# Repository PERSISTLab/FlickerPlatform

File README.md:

Flicker Platform
======
 This repository hosts the Flicker platform acompanying the paper titled [*Flicker: Rapid Prototyping for the Batteryless Internet-of-Things*](http://josiahhester.com/cv/files/flickersensys.pdf) in the 15th ACM Conference on Embedded Networked Sensor Systems [(SenSys 2017)](http://sensys.acm.org/2017/).

This project is part of an ongoing collaboration between Clemson University and Northwestern University, originally initiated at Clemson under Prof. Jacob Sorber, with Josiah Hester.

## Setup and Usage

Please note that this is older hardware useful for posterity and documenting ideas. More modern platforms are currently in develop with richer documentation and examples.

## Contributors

- Diana Zhang and  Tamara Ortega contributed early on to the Flicker hardware designs for an REU in the summer of 2014.
- [Prof. Josiah Hester](http://josiahhester.com/cv/) guided the early effort and continued on after summer as a graduate student in the PERSIST Lab, implementing the compiler and supporting systems. Prof. Hester continues this work at Northwestern University.
- [Prof. Jacob Sorber](https://people.cs.clemson.edu/~jsorber/) oversaw, funded, and originated the project.

## Funding 

This research is based upon work supported by the National Science Foundation under grants [CNS-1453607](https://nsf.gov/awardsearch/showAward?AWD_ID=1453607) and [CCF-1539536](https://www.nsf.gov/awardsearch/showAward?AWD_ID=1539536) Any opinions, findings, and conclusions or recommendations expressed in this material are those of the authors and do not necessarily reflect the views of the National Science Foundation

## License

	MIT License
	Copyright 2017 Josiah Hester, Jacob Sorber, Clemson University

	Permission is hereby granted, free of charge, to any person obtaining a copy of this 
	software and associated documentation files (the "Software"), to deal in the Software 
	without restriction, including without limitation the rights to use, copy, modify, merge, 
	publish, distribute, sublicense, and/or sell copies of the Software, and to permit persons 
	to whom the Software is furnished to do so, subject to the following conditions:

	The above copyright notice and this permission notice shall be included in all copies or 
	substantial portions of the Software.

	THE SOFTWARE IS PROVIDED "AS IS", WITHOUT WARRANTY OF ANY KIND, EXPRESS OR IMPLIED, 
	INCLUDING BUT NOT LIMITED TO THE WARRANTIES OF MERCHANTABILITY, FITNESS FOR A PARTICULAR 
	PURPOSE AND NONINFRINGEMENT. IN NO EVENT SHALL THE AUTHORS OR COPYRIGHT HOLDERS BE LIABLE 
	FOR ANY CLAIM, DAMAGES OR OTHER LIABILITY, WHETHER IN AN ACTION OF CONTRACT, TORT OR 
	OTHERWISE, ARISING FROM, OUT OF OR IN CONNECTION WITH THE SOFTWARE OR THE USE OR OTHER 
	DEALINGS IN THE SOFTWARE.

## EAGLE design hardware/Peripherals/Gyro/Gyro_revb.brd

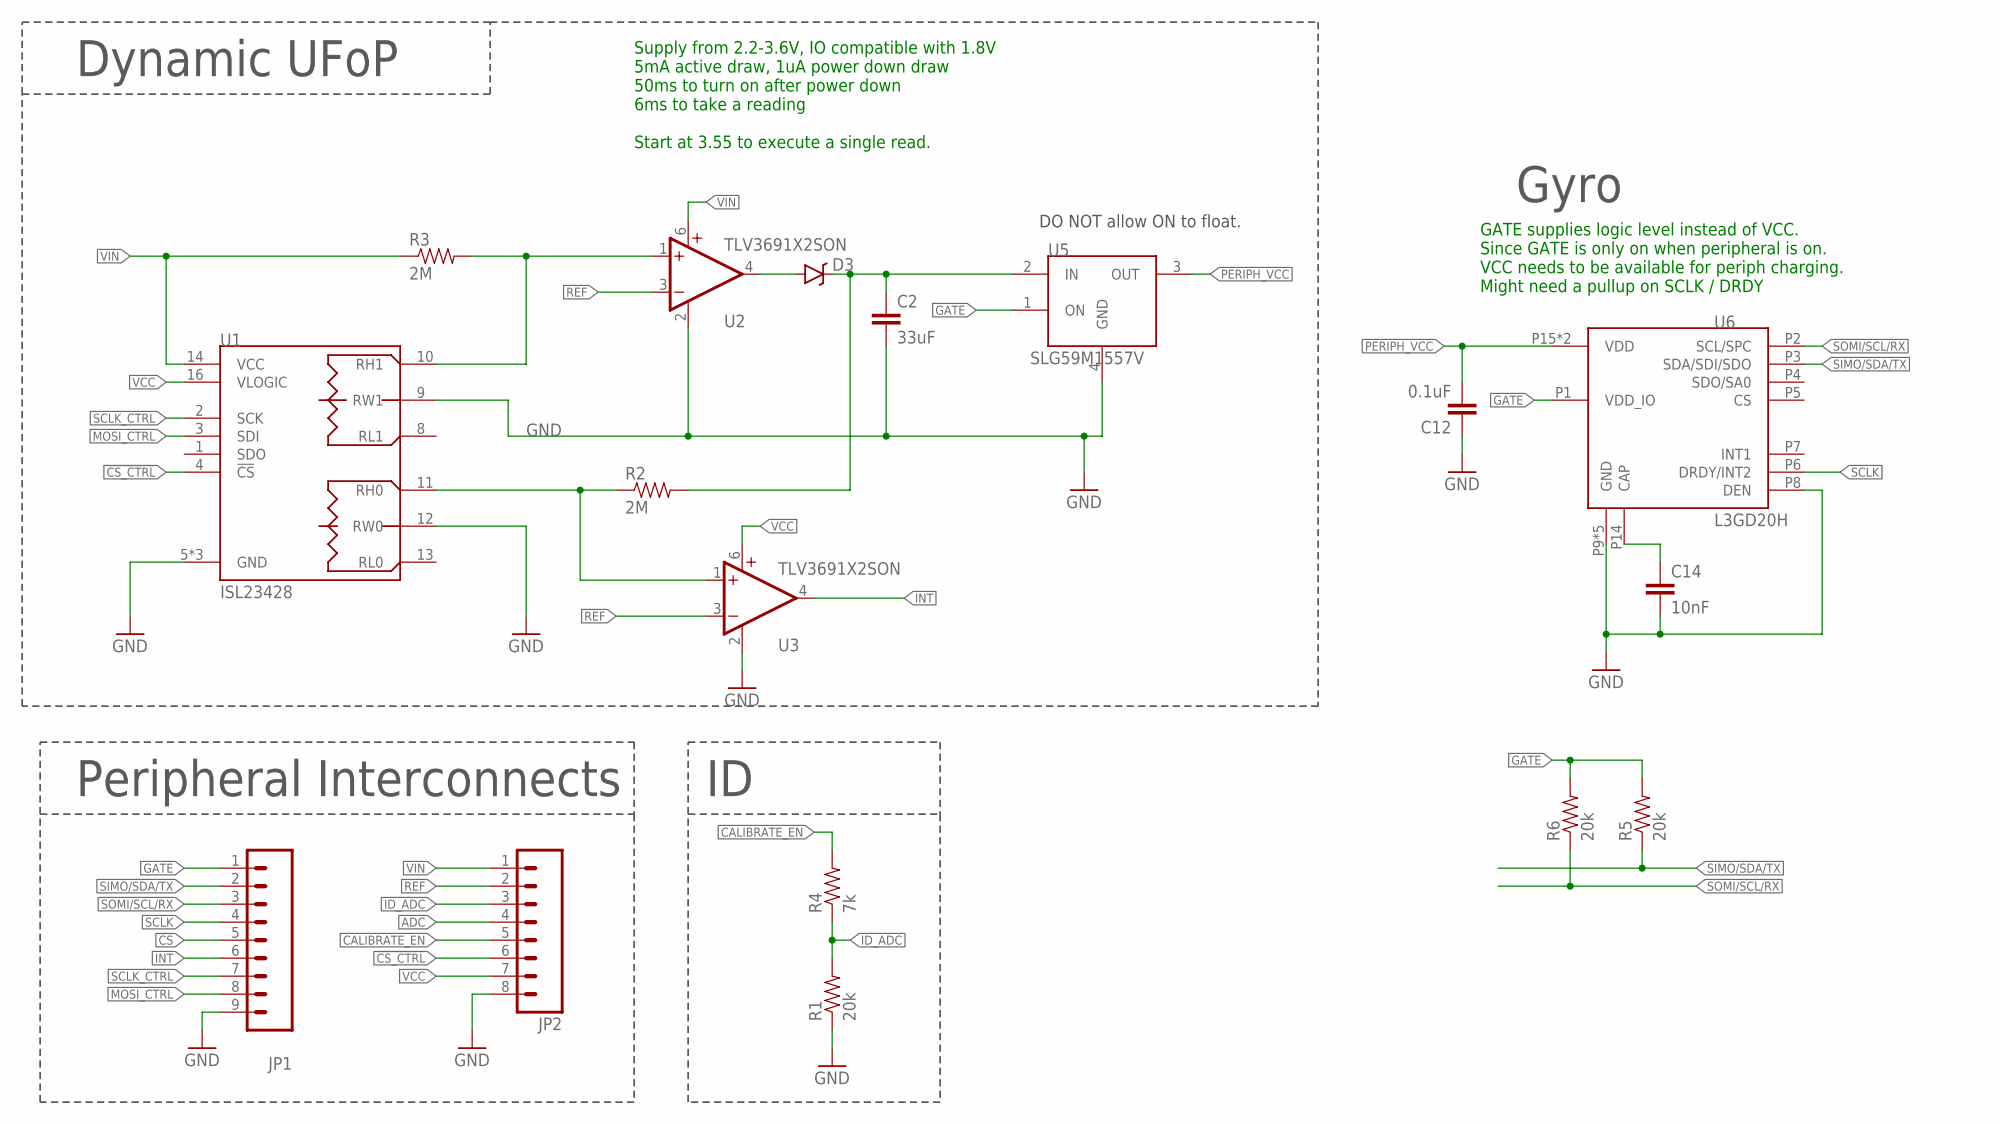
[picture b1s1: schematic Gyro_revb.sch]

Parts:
C2: 33uF; 1206; MPN C3216X5R0J336M130AC; DIGIKEY 445-4060-1-ND
C12: 0.1uF; 0402; MANAFACTURERPARTNUMBER 0402YD104KAT2A
C14: 10nF; 0402; MPN 0402YC103KAT2A
D3: RB751; SOD-523; MPN BAS40-02V-V-G-08; DIGIKEY BAS40-02V-V-G-08GICT-ND
JP1: M091.27MM; 1X09-1.27MM; MANUFACTURERPARTNUMBER GRPB091VWVN-RC; DIGIKEY S9014E-09-ND
JP2: M081.27MM; 1X08-1.27MM; MANUFACTURERPARTNUMBER GRPB081VWVN-RC; DIGIKEY S9014E-08-ND
R1, R5, R6: 20k; 0402; MPN ERJ-2RKF2002X
R2, R3: 2M; 0402; MPN RC1005F205CS; DIGIKEY 1276-4293-1-ND
R4: 7k; 0402; MPN RC0402FR-077K15L
U1: ISL23428; UTQFN-16; MPN ISL23428TFRUZ-T7A; DIGIKEY ISL23428TFRUZ-T7ACT-ND
U2, U3: TLV3691X2SON; X2SON; MPN TLV3691IDPFR; DIGIKEY 296-37242-1-ND
U5: SLG59M1557V; 4STDFN; MPN SLG59M1557V; MOUSER 402-SLG59M1557V
U6: L3GD20H; LGA16L; MPN L3GD20HTR; DIGIKEY 497-13931-1-ND

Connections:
!CS: JP1.5
!CS_CTRL: JP2.6, U1.4 (!CS)
ADC: JP2.4
CALIBRATE_EN: JP2.5, R4.2
GATE: JP1.1, R5.2, R6.2, U5.1 (ON), U6.P1 (VDD_IO)
GND: C2.2, C12.1, C14.2, JP1.9, JP2.8, R1.1, U1.5 (GND), U1.6 (GND), U1.9 (RW1), U1.12 (RW0), U1.15 (GND), U2.2 (GND), U3.2 (GND), U5.4 (GND), U6.P8 (DEN), U6.P9 (GND), U6.P10 (GND), U6.P11 (GND), U6.P12 (GND), U6.P13 (GND)
ID_ADC: JP2.3, R1.2, R4.1
INT: JP1.6, U3.4 (OUT)
MOSI_CTRL: JP1.8, U1.3 (SDI)
unnamed: D3.A, U2.4 (OUT)
unnamed: C2.1, D3.C, R2.2, U5.2 (IN)
unnamed: R3.2, U1.10 (RH1), U2.1 (+IN)
unnamed: R2.1, U1.11 (RH0), U3.1 (+IN)
unnamed: C14.1, U6.P14 (CAP)
PERIPH_VCC: C12.2, U5.3 (OUT), U6.P15 (VDD), U6.P16 (VDD)
REF: JP2.2, U2.3 (-IN), U3.3 (-IN)
SCLK: JP1.4, U6.P6 (DRDY/INT2)
SCLK_CTRL: JP1.7, U1.2 (SCK)
SIMO/SDA/TX: JP1.2, R5.1, U6.P3 (SDA/SDI/SDO)
SOMI/SCL/RX: JP1.3, R6.1, U6.P2 (SCL/SPC)
VCC: JP2.7, U1.16 (VLOGIC), U3.6 (V+)
VIN: JP2.1, R3.1, U1.14 (VCC), U2.6 (V+)

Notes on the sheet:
DO NOT allow ON to float.
Peripheral Interconnects
Dynamic UFoP
Gyro
GATE supplies logic level instead of VCC. Since GATE is only on when peripheral is on. VCC needs to be available for periph charging. Might need a pullup on SCLK / DRDY
Supply from 2.2-3.6V, IO compatible with 1.8V 5mA active draw, 1uA power down draw 50ms to turn on after power down 6ms to take a reading Start at 3.55 to execute a single read.

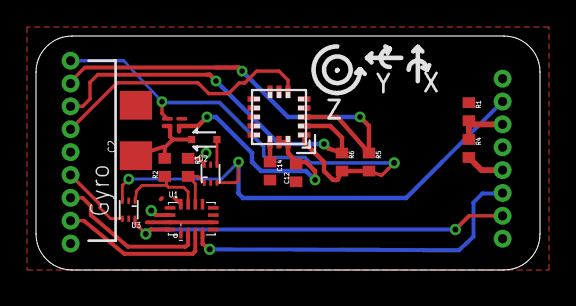
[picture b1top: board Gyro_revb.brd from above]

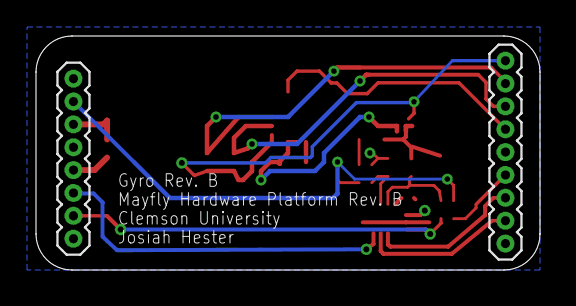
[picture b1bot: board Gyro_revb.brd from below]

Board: 2 copper layers, 28.0 x 13.0 mm, 17 parts (2 on the bottom side), 20 nets.

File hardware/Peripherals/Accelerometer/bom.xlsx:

Part | Value | Device | Package | Description | DIGIKEY | MPN
C2 | 2.2uF | C-EU0603 | 603 |  | 587-1430-1-ND | EMK107BJ225KA-T
C12 | 0.1uF | C-EU | 402 |  |  | 0402YD104KAT2A
D3 | RB751 | DIODE-SCHOTTKY-RB751 | SOD-523 | Schottky diodes in SFE's production catalog | BAS40-02V-V-G-08GICT-ND | BAS40-02V-V-G-08
JP1 |  | M091.27MM | 1X09-1.27MM | Header 9 | S9014E-09-ND | GRPB091VWVN-RC
JP2 |  | M081.27MM | 1X08-1.27MM | Header 8 | S9014E-08-ND | GRPB081VWVN-RC
R1 | 20k | R-EU | 402 |  |  | ERJ-2RKF2002X
R2 | 2M | R-EU | 402 |  | 1276-4293-1-ND | RC1005F205CS
R3 | 2M | R-EU | 402 |  | 1276-4293-1-ND | RC1005F205CS
R4 | 1k | R-EU | 402 |  |  | ERJ-2RKF1001X
U1 | ISL23428 | ISL23428 | UTQFN-16 | Intersil: Dual, 128-Tap, Low Voltage Digitally Controlled | ISL23428TFRUZ-T7ACT-ND | ISL23428TFRUZ-T7A
U2 | TLV3691X2SON | TLV3691X2SON | X2SON | 0.9-V to 6.5-V, Nanopower Comparator | 296-37242-1-ND | TLV3691IDPFR
U3 | TLV3691X2SON | TLV3691X2SON | X2SON | 0.9-V to 6.5-V, Nanopower Comparator | 296-37242-1-ND | TLV3691IDPFR
U4 | ADXL362 | ADXL362 | ADXL362 | Micropower 3-axis accelerometer | ADXL362BCCZ-RL7CT-ND | ADXL362BCCZ-RL7
;";";
U5 | SLG59M1557V | SLG59M1557V | 4STDFN | SILEGO SLG59M1557V: Ultra-small 28.5 mŒ©, 1.0 A |  | SLG59M1557V

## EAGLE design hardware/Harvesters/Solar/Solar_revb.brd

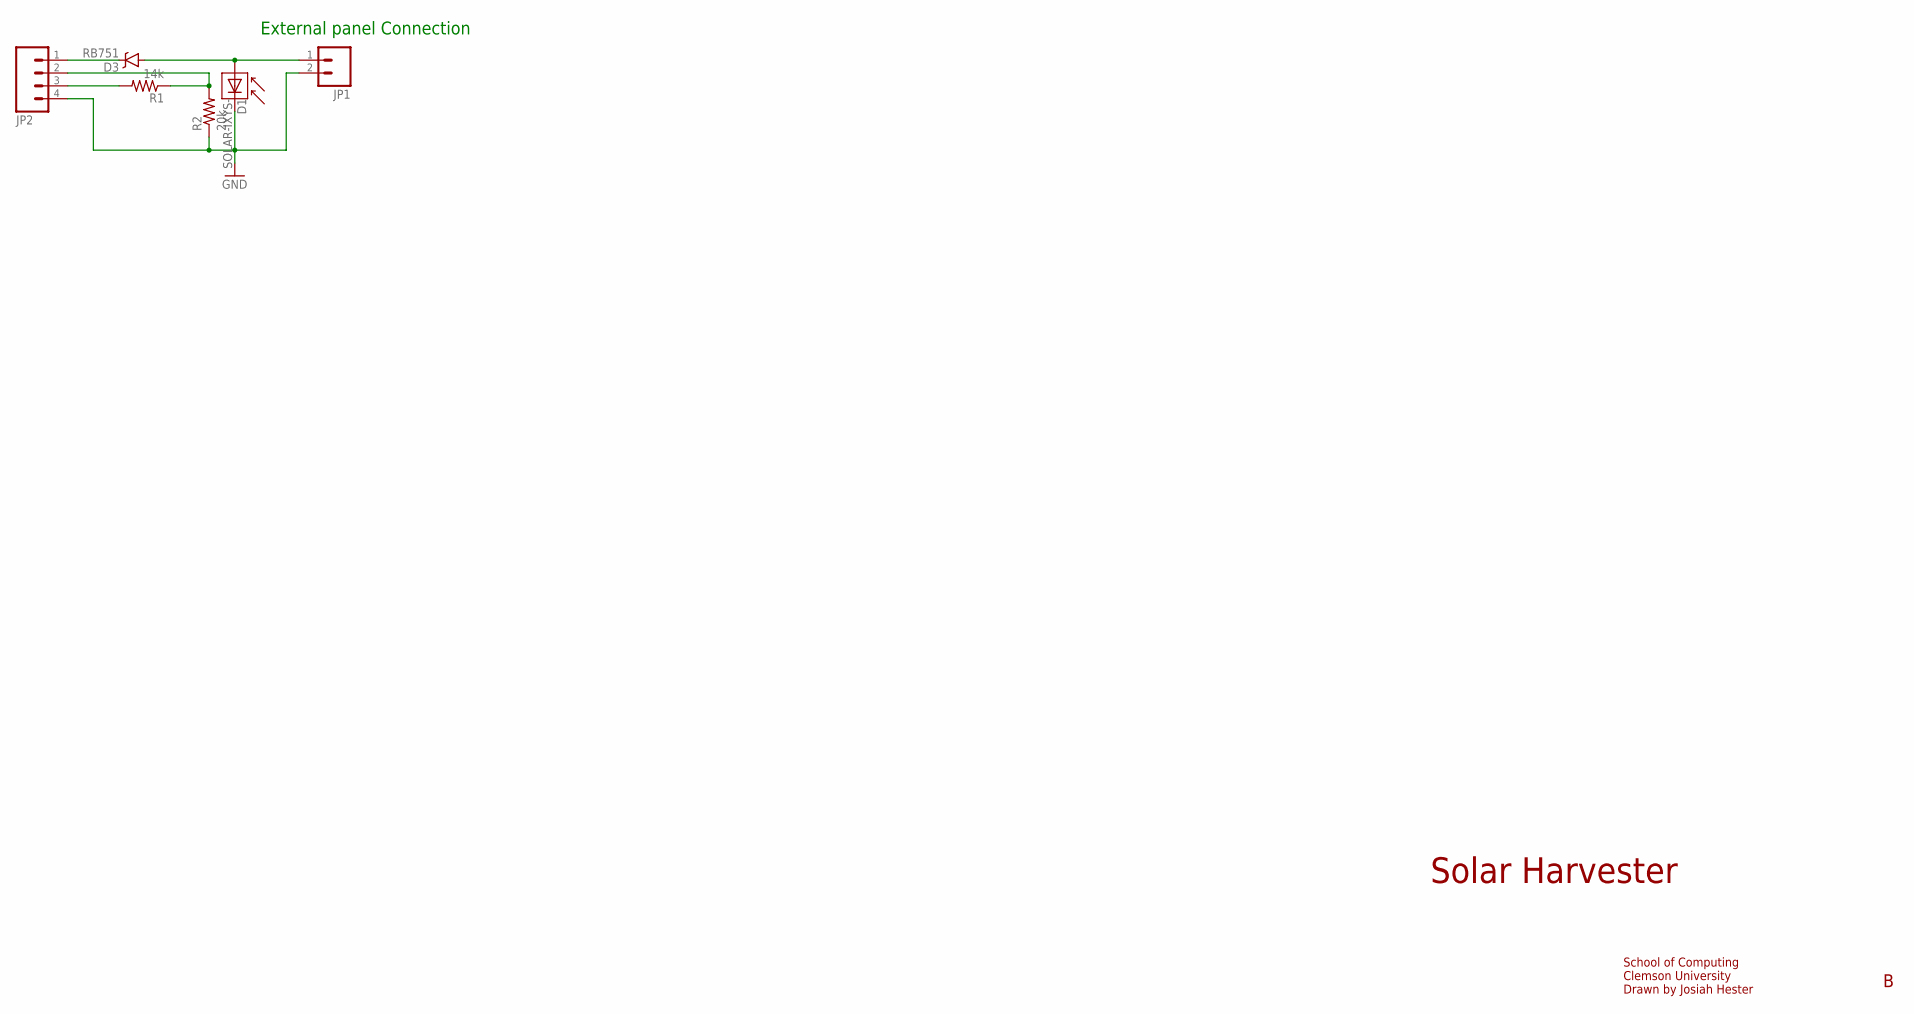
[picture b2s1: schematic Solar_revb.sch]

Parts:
D1: SOLAR-IXYS-; SOLARBIT-12X1; DIGIKEY KXOB22-01X8F-ND
D3: RB751; SOD-523; MPN BAS40-02V-V-G-08
JP1: M02LOCK; 1X02_LOCK
JP2: M041.27MM; 1X04-1.27MM; MPN GRPB041VWVN-RC
R1: 14k; 0603; MPN CRCW060314K0FKEA
R2: 20k; 0603; MPN CRCW060320K0FKEA

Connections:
GND: D1.- (C), JP1.2, JP2.4, R2.1
unnamed: JP2.2, R1.1, R2.2
unnamed: D1.+ (A), D3.A, JP1.1
unnamed: JP2.3, R1.2
unnamed: D3.C, JP2.1

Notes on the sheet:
Solar Harvester
School of Computing Clemson University Drawn by Josiah Hester
External panel Connection

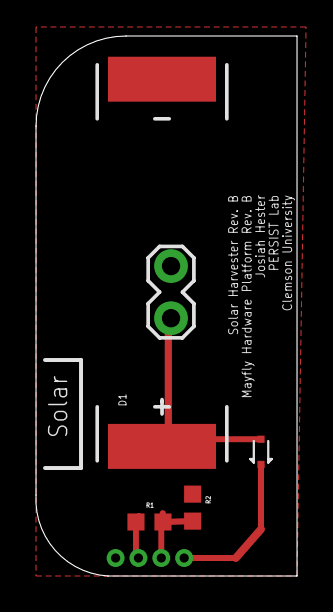
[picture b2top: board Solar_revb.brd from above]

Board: 2 copper layers, 14.5 x 30.0 mm, 6 parts (1 on the bottom side), 5 nets.

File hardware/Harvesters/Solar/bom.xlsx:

Part | Value | Device | Package | Description | DIGIKEY | MPN | PROD_ID | VALUE
D1 | SOLAR-IXYS- | SOLAR-IXYS- | SOLARBIT-12X1 |  | KXOB22-01X8F-ND
D3 | RB751 | DIODE-SCHOTTKY-RB751 | SOD-523 | Schottky diodes in SFE's production catalog |  | BAS40-02V-V-G-08 | DIO-11018 | RB751
JP1 |  | M02LOCK | 1X02_LOCK | Standard 2-pin 0.1 header. Use with"
JP2 |  | M041.27MM | 1X04-1.27MM | Header 4 |  | GRPB041VWVN-RC
R1 | 14k | R-EU0603 | 603 |  |  | CRCW060314K0FKEA
R2 | 20k | R-EU0603 | 603 |  |  | CRCW060320K0FKEA

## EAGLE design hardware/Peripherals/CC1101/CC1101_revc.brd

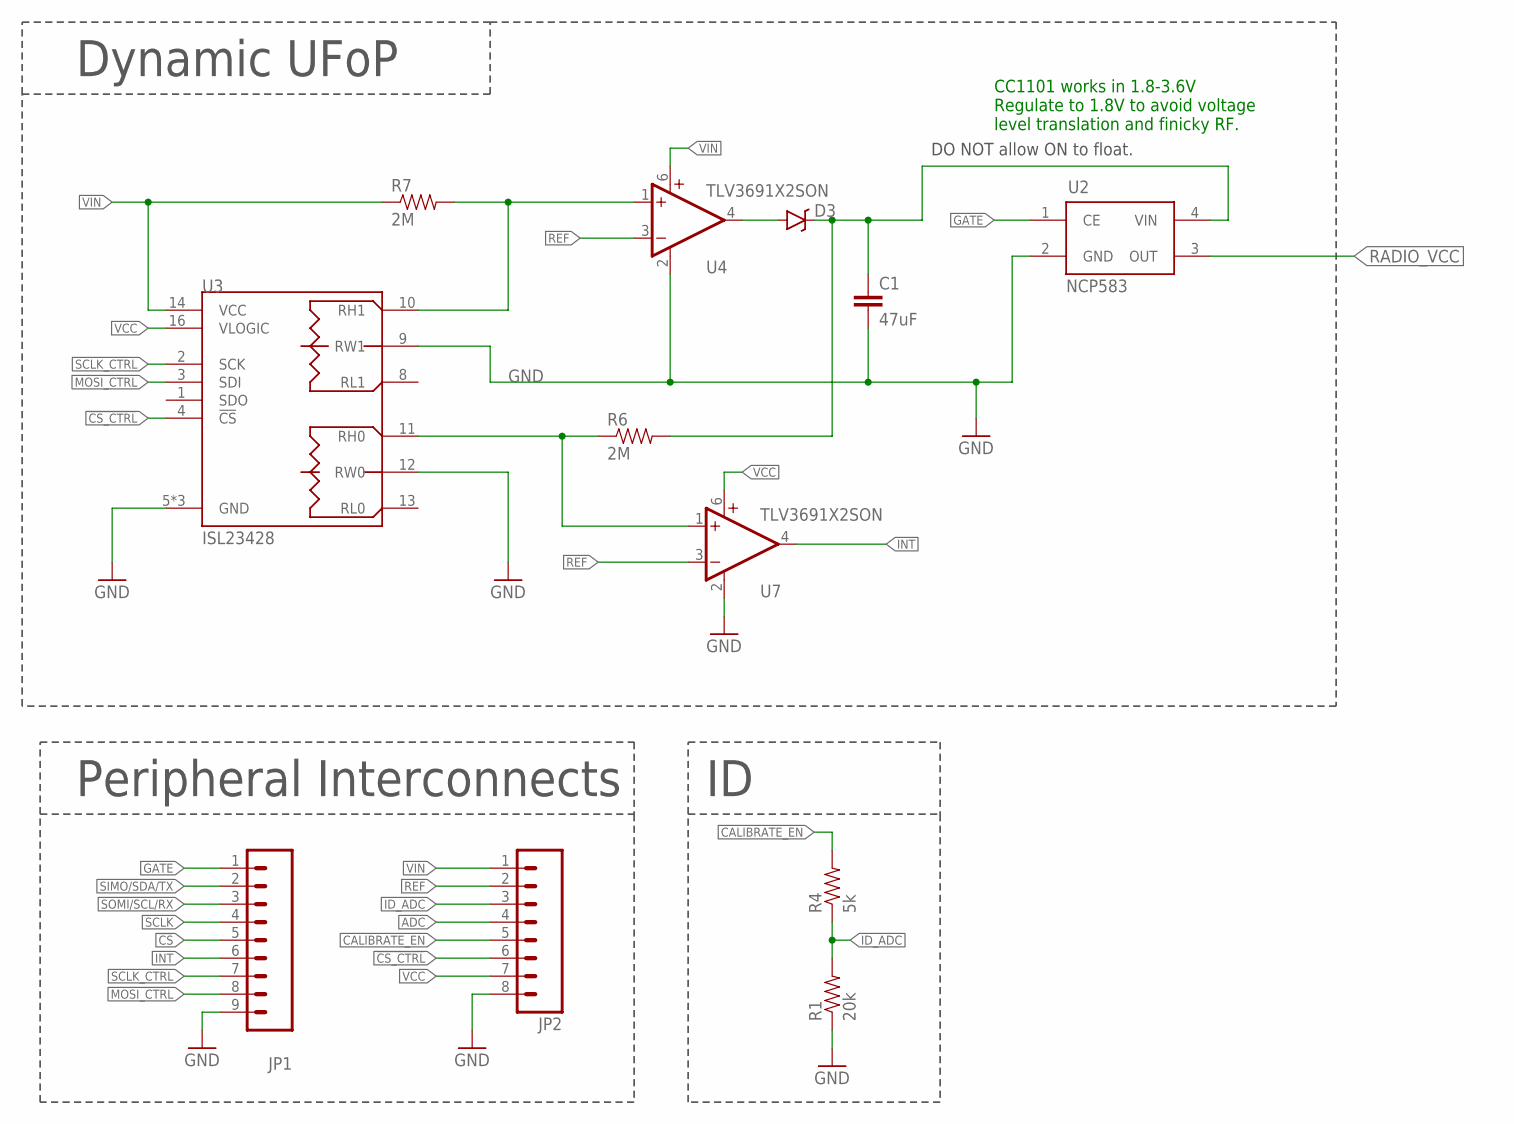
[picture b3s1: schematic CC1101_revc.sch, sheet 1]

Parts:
C1: 47uF; 1206; MPN GRM31CR60J476ME19L; DIGIKEY 490-3907-1-ND
D3: RB751; SOD-523; MPN RB751S40T1G; DIGIKEY BAS40-02V-V-G-08GICT-ND
JP1: M091.27MM; 1X09-1.27MM; MPN GRPB091VWVN-RC
JP2: M081.27MM; 1X08-1.27MM; MPN GRPB081VWVN-RC
R1: 20k; 0402; MPN ERJ-2RKF2002X
R4: 5k; 0402; MPN ERJ-2RKF4991X
R6, R7: 2M; 0402; MPN RC1005F205CS; DIGIKEY 1276-4293-1-ND
U2: NCP583; SC82-AB_1PRIMARY; MPN NCP583SQ18T1G; DIGIKEY NCP583SQ18T1GOSCT-ND
U3: ISL23428; UTQFN-16; MPN ISL23428TFRUZ-T7A; DIGIKEY ISL23428TFRUZ-T7ACT-ND
U4, U7: TLV3691X2SON; X2SON; MPN TLV3691IDPFR; DIGIKEY 296-37242-1-ND

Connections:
!CS: JP1.5; also elsewhere on the board
!CS_CTRL: JP2.6, U3.4 (!CS)
ADC: JP2.4
CALIBRATE_EN: JP2.5, R4.2
GATE: JP1.1, U2.1 (CE)
GND: C1.2, JP1.9, JP2.8, R1.1, U2.2 (GND), U3.5 (GND), U3.6 (GND), U3.9 (RW1), U3.12 (RW0), U3.15 (GND), U4.2 (GND), U7.2 (GND); also elsewhere on the board
ID_ADC: JP2.3, R1.2, R4.1
INT: JP1.6, U7.4 (OUT)
MOSI_CTRL: JP1.8, U3.3 (SDI)
unnamed: R7.2, U3.10 (RH1), U4.1 (+IN)
unnamed: R6.1, U3.11 (RH0), U7.1 (+IN)
unnamed: D3.A, U4.4 (OUT)
PERIPH_VCC: C1.1, D3.C, R6.2, U2.4 (VIN)
RADIO_VCC: U2.3 (OUT); also elsewhere on the board
REF: JP2.2, U4.3 (-IN), U7.3 (-IN)
SCLK: JP1.4; also elsewhere on the board
SCLK_CTRL: JP1.7, U3.2 (SCK)
SIMO/SDA/TX: JP1.2; also elsewhere on the board
SOMI/SCL/RX: JP1.3; also elsewhere on the board
VCC: JP2.7, U3.16 (VLOGIC), U7.6 (V+)
VIN: JP2.1, R7.1, U3.14 (VCC), U4.6 (V+)

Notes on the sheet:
Peripheral Interconnects
Dynamic UFoP
DO NOT allow ON to float.
CC1101 works in 1.8-3.6V Regulate to 1.8V to avoid voltage level translation and finicky RF.

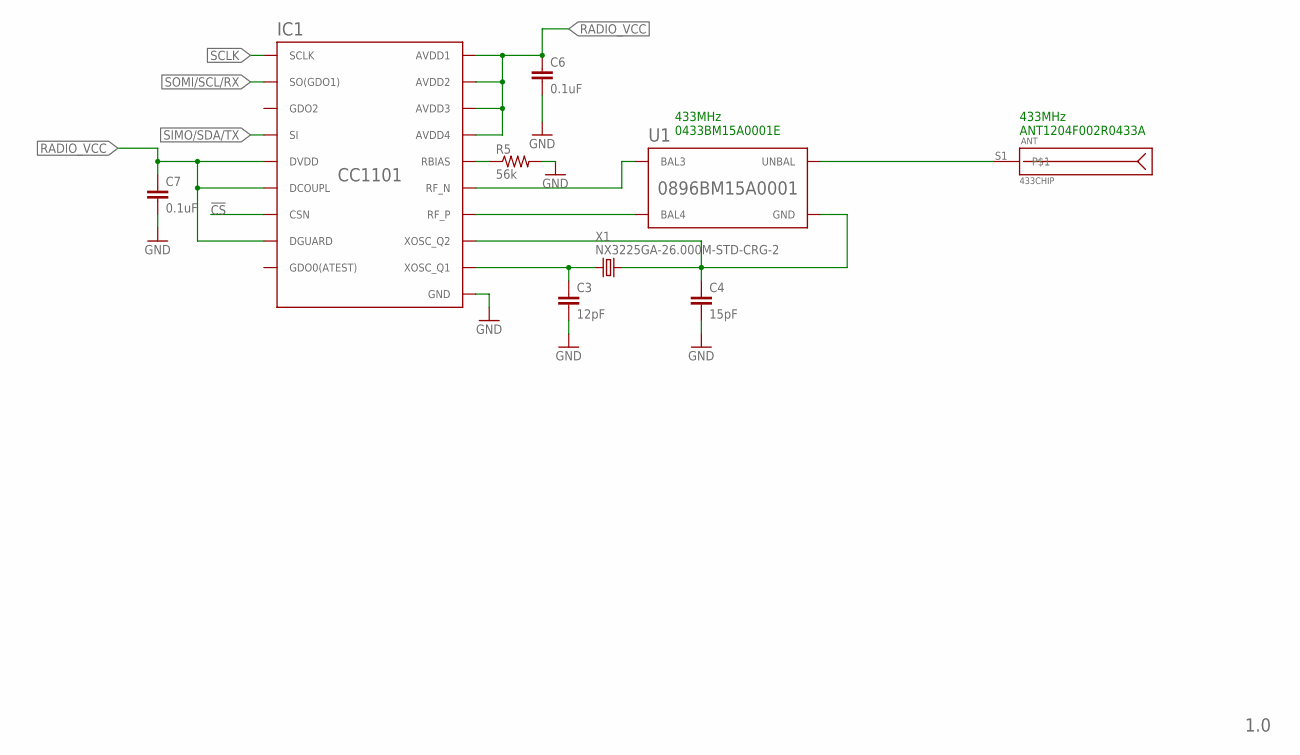
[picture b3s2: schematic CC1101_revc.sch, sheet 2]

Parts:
ANT: 433CHIP; ANT-433-USP; MPN ANT1204F002R0433A
C3: 12pF; 0603; MPN 06035A120FAT2A
C4: 15pF; 0603; MPN C1608C0G1H150J080AA
C6, C7: 0.1uF; 0603; MPN GCJ188R71H104KA12D
IC1: CC1101; QLP20; MPN CC1101RGP
R5: 56k; 0603; MPN ERJ-3GEYJ563V
U1: 0896BM15A0001; MPN 0433BM15A0001E
X1: NX3225GA-26.000M-STD-CRG-2; XTAL-3.2X2.5; MPN NX3225GA-26.000M-STD-CRG-2

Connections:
!CS: IC1.7 (CSN); also elsewhere on the board
GND: C3.2, C4.2, C6.2, C7.2, IC1.16 (GND), IC1.19 (GND), IC1.GND, R5.2; also elsewhere on the board
unnamed: IC1.12 (RF_P), U1.4 (BAL4)
unnamed: IC1.13 (RF_N), U1.3 (BAL3)
unnamed: C3.1, IC1.8 (XOSC_Q1), X1.1
unnamed: IC1.17 (RBIAS), R5.1
unnamed: ANT.S1, U1.1 (UNBAL)
RADIO_VCC: C6.1, C7.1, IC1.4 (DVDD), IC1.5 (DCOUPL), IC1.9 (AVDD1), IC1.11 (AVDD2), IC1.14 (AVDD3), IC1.15 (AVDD4), IC1.18 (DGUARD); also elsewhere on the board
SCLK: IC1.1 (SCLK); also elsewhere on the board
SIMO/SDA/TX: IC1.20 (SI); also elsewhere on the board
SOMI/SCL/RX: IC1.2 (SO(GDO1)); also elsewhere on the board
XOSC_Q2: C4.1, IC1.10 (XOSC_Q2), U1.2 (GND), U1.5 (GND), U1.6 (GND), X1.3 (2)

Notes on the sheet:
433MHz 0433BM15A0001E
1.0
433MHz ANT1204F002R0433A

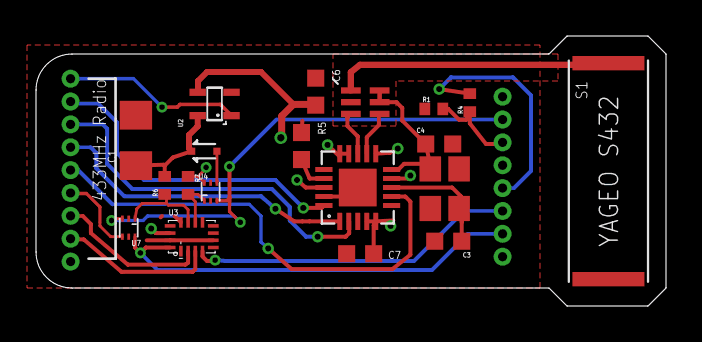
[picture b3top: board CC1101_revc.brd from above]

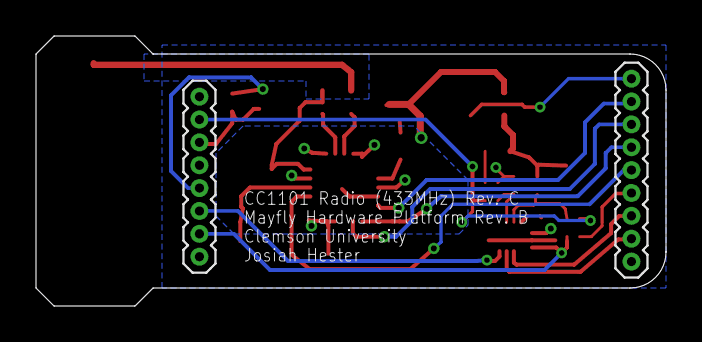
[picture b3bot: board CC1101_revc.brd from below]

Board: 2 copper layers, 35.0 x 15.0 mm, 21 parts (2 on the bottom side), 26 nets.

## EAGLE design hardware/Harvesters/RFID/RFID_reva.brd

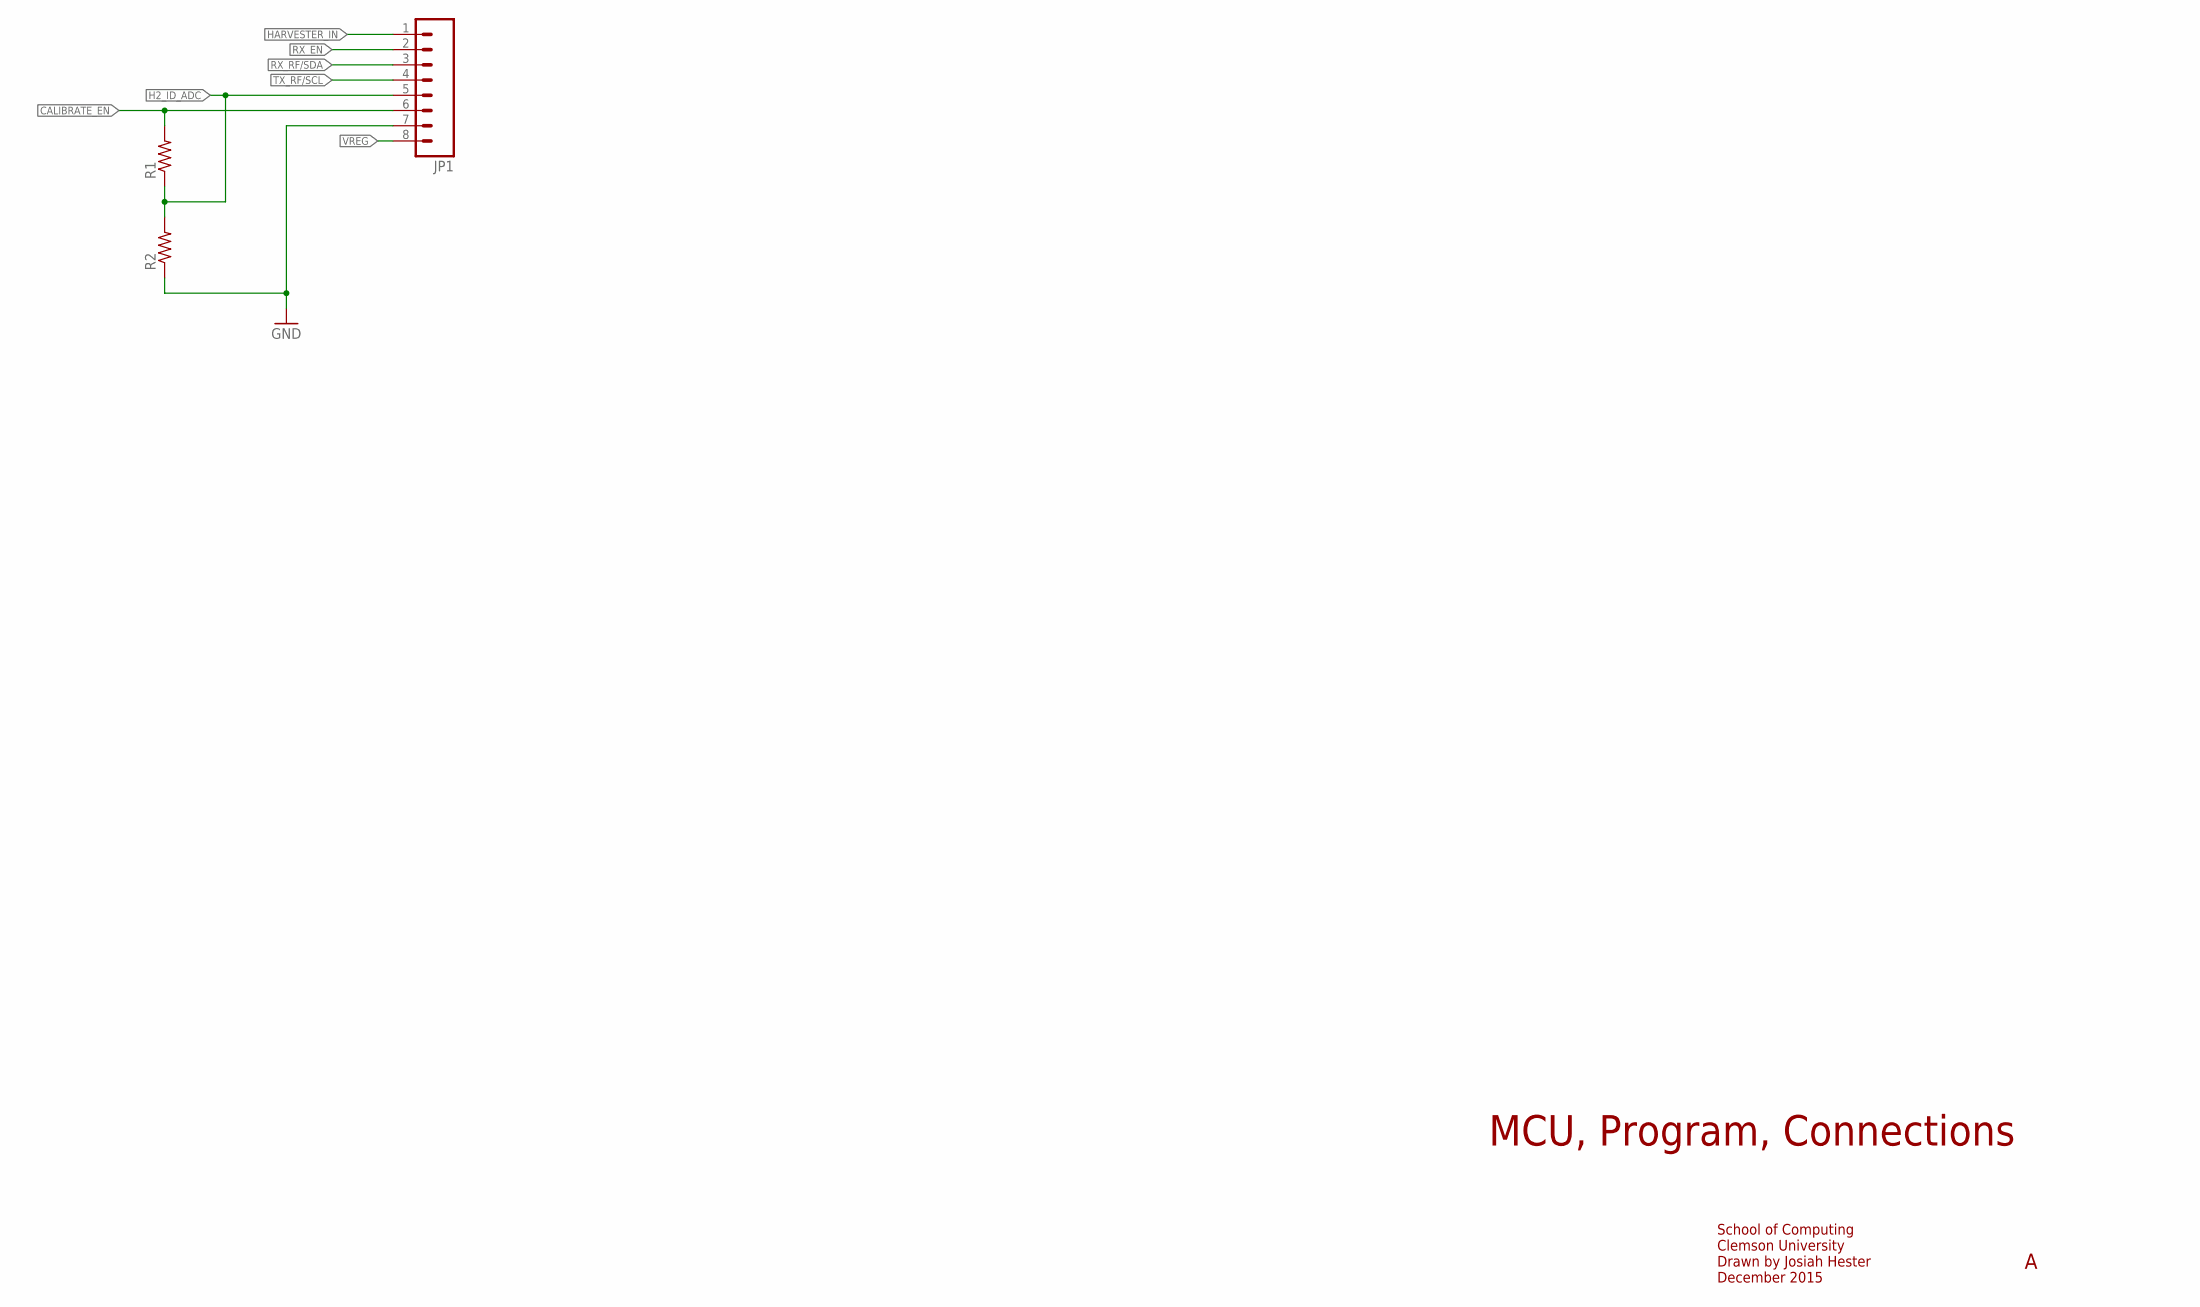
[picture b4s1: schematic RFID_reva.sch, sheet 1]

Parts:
JP1: M081.27MM; 1X08-1.27MM; DIGIKEY 1212-1352-ND
R1, R2: R-EU0603; 0603

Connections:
CALIBRATE_EN: JP1.6, R1.2
GND: JP1.7, R2.1; also elsewhere on the board
H2_ID_ADC: JP1.5, R1.1, R2.2
HARVESTER_IN: JP1.1; also elsewhere on the board
RX_EN: JP1.2; also elsewhere on the board
RX_RF/SDA: JP1.3; also elsewhere on the board
TX_RF/SCL: JP1.4; also elsewhere on the board
VREG: JP1.8; also elsewhere on the board

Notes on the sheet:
MCU, Program, Connections
School of Computing Clemson University Drawn by Josiah Hester December 2015

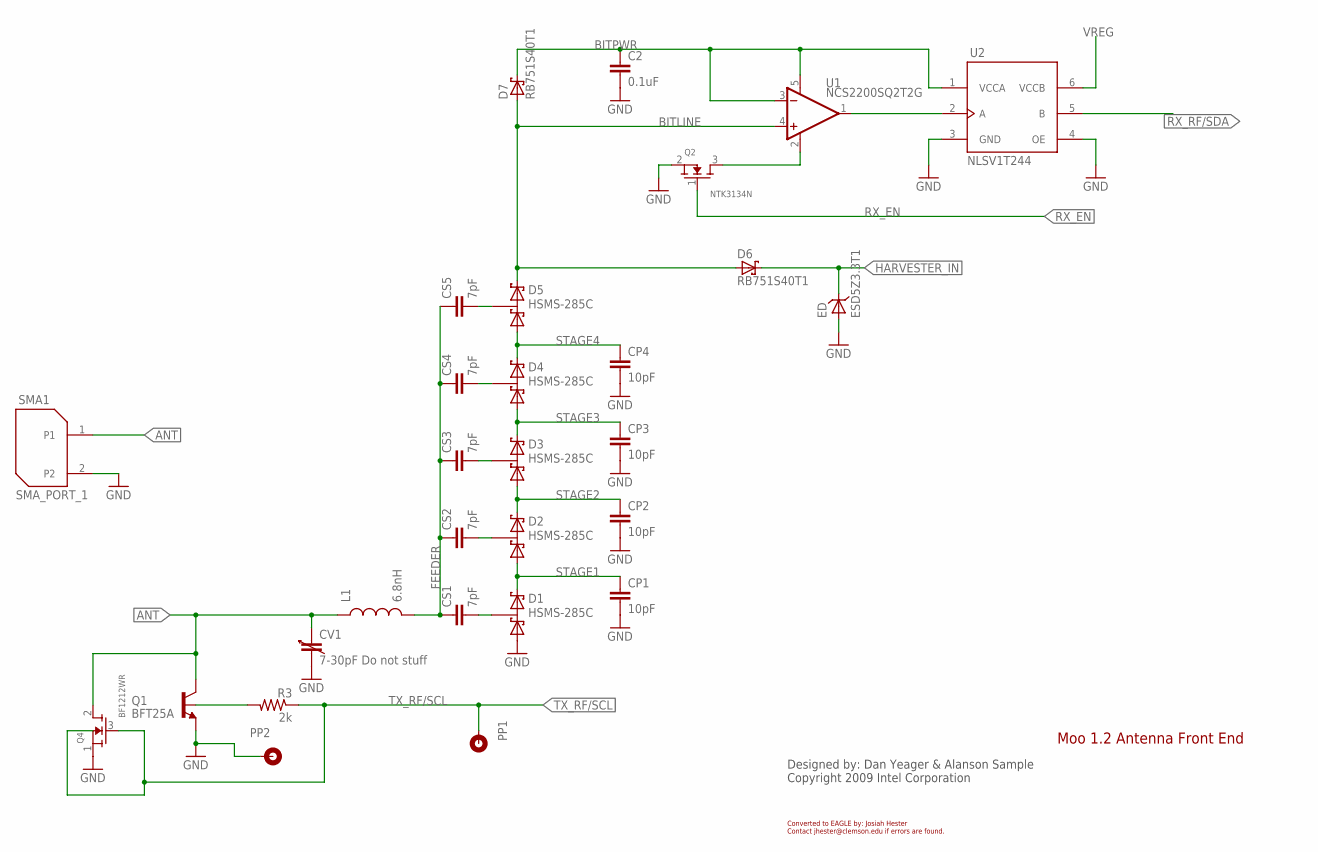
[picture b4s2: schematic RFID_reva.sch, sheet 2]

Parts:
C2: 0.1uF; 0402_1PRIMARY
CP1, CP2, CP3, CP4: 10pF; 0402_1PRIMARY
CS1, CS2, CS3: 7pF; 0402_1PRIMARY; DIGIKEY 490-5878-1-ND
CS4, CS5: 7pF; 0402_1PRIMARY
CV1: 7-30pF Do not stuff; VAR-CAP_603_1PRIMARY
D1, D2, D3, D4, D5: HSMS-285C; SOT-323,_HSMS-285C_1PRIMARY
D6, D7: RB751S40T1; SOD-523_1PRIMARY
ED: ESD5Z3.3T1; SOD-523_1PRIMARY
L1: 6.8nH; 0603_1PRIMARY
PP1: PROBE_POINT_2; PROBE_POINT_2PRIMARY
PP2: PROBE_POINT_1; PROBE_POINT_2PRIMARY
Q1: BFT25A; SOT-23_1PRIMARY; DIGIKEY 568-1992-1-ND
Q2: NTK3134N; SOT723_1PRIMARY
Q4: BF1212WR; SOT343R_1PRIMARY
R3: 2k; 0402_1PRIMARY
SMA1: SMA_PORT_1; SMA_PORT_1PRIMARY
U1: NCS2200SQ2T2G; SC70-5_1PRIMARY
U2: NLSV1T244; UDFN6_1PRIMARY

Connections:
ANT: CV1.1, L1.1, Q1.3 (C), Q4.2 (3), SMA1.1
BITLINE: D5.2, D6.2 (A), D7.2 (A), U1.4
BITPWR: C2.1, D7.1 (C), U1.3, U1.5, U2.1 (VCCA)
CONTROL: Q1.1 (B), R3.1 (2)
FEEDER: CS1.1, CS2.1, CS3.1, CS4.1, CS5.1, L1.2
GND: C2.2, CP1.2, CP2.2, CP3.2, CP4.2, CV1.2, D1.1, ED.2, PP2.1, Q1.2 (E), Q2.2, Q4.1 (2), SMA1.2, U2.3 (GND), U2.4 (OE); also elsewhere on the board
HARVESTER_IN: D6.1 (C), ED.1; also elsewhere on the board
unnamed: U1.1, U2.2 (A)
unnamed: Q2.3, U1.2
NETCS1_2: CS1.2, D1.3
NETCS2_2: CS2.2, D2.3
NETCS3_2: CS3.2, D3.3
NETCS4_2: CS4.2, D4.3
NETCS5_2: CS5.2, D5.3
RX_EN: Q2.1; also elsewhere on the board
RX_RF/SDA: U2.5 (B); also elsewhere on the board
STAGE1: CP1.1, D1.2, D2.1
STAGE2: CP2.1, D2.2, D3.1
STAGE3: CP3.1, D3.2, D4.1
STAGE4: CP4.1, D4.2, D5.1
TX_RF/SCL: PP1.1, Q4.3 (1), Q4.4, R3.2 (1); also elsewhere on the board
VREG: U2.6 (VCCB); also elsewhere on the board

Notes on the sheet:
Designed by: Dan Yeager & Alanson Sample Copyright 2009 Intel Corporation
Moo 1.2 Antenna Front End
Converted to EAGLE by: Josiah Hester Contact jhester@clemson.edu if errors are found.

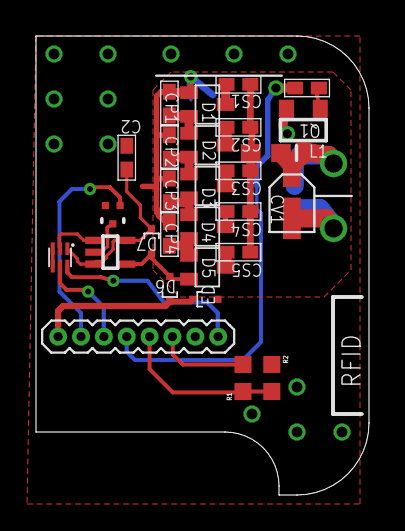
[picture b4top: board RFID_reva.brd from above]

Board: 2 copper layers, 18.5 x 25.5 mm, 32 parts (1 on the bottom side), 24 nets.

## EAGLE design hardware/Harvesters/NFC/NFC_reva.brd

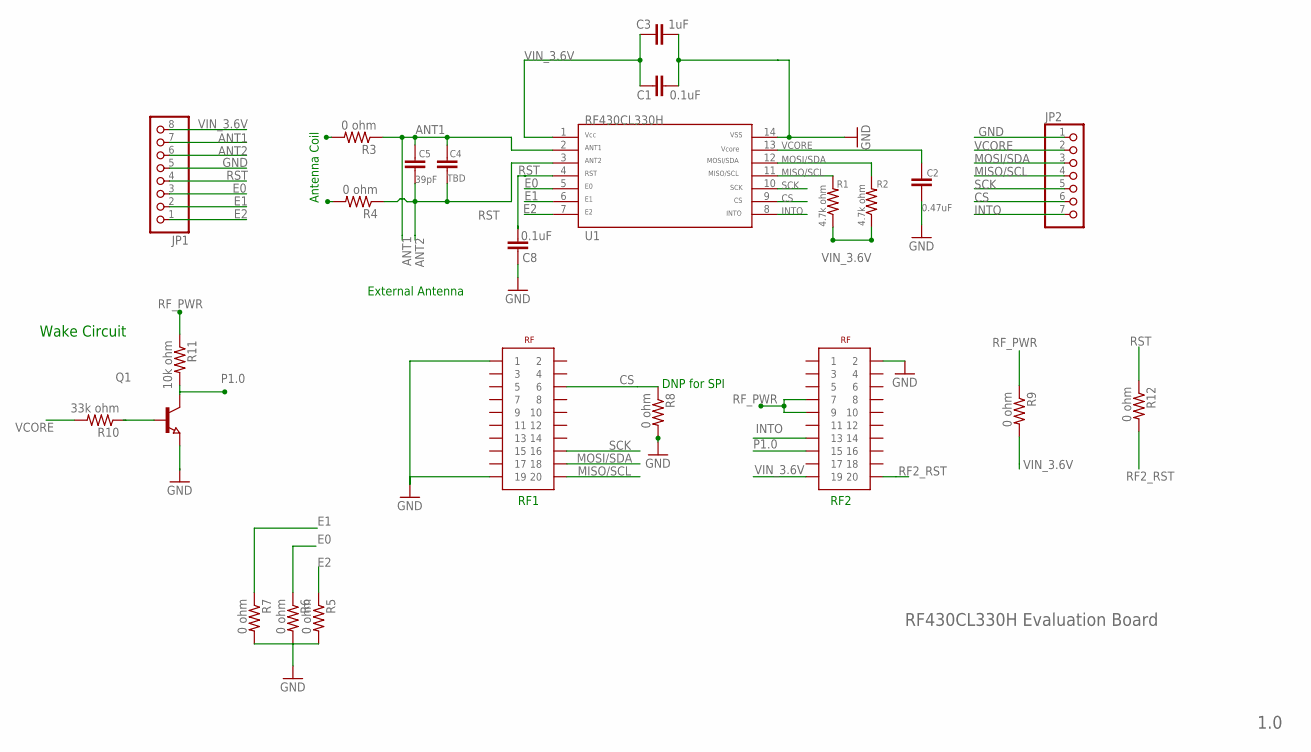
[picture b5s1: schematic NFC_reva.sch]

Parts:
C1, C8: 0.1uF; C0603
C2: 0.47uF; C0603
C3: 1uF; C0603
C4: TBD; C0603
C5: 39pF; C0603
JP1: PINHD-1X8; 1X08
JP2: PINHD-1X7; 1X07
Q1: NPN-TRANSISTOR_SOT23; SOT23
R1, R2: 4.7k ohm; R0402
R3, R4, R5, R6, R7, R8, R9, R12: 0 ohm; R0402
R10: 33k ohm; R0402
R11: 10k ohm; R0402
RF_HEADER: EM_HEADER; TFM-110-02-SM-D-A-K
U1: RF430CL330H; PW14

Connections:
ANT1: C4.1, C5.1, JP1.7, R3.1, U1.2
ANT2: C4.2, C5.2, JP1.6, R4.1, U1.3
CS: JP2.6, R8.1, RF_HEADER.6, U1.9
E0: JP1.3, R6.1, U1.5
E1: JP1.2, R7.1, U1.6
E2: JP1.1, R5.1, U1.7
GND: C1.2, C2.2, C3.2, C8.1, JP1.5, JP2.1, Q1.2 (E), R5.2, R6.2, R7.2, R8.2, RF_HEADER.1, RF_HEADER.19, RF_HEADER.22 (2), U1.14
INTO: JP2.7, RF_HEADER.33 (13), U1.8
MISO/SCL: JP2.4, R1.2, RF_HEADER.20, U1.11
MOSI/SDA: JP2.3, R2.2, RF_HEADER.18, U1.12
unnamed: Q1.1 (B), R10.1
P1.0: Q1.3 (C), R11.2, RF_HEADER.35 (15)
RF2_RST: R12.2, RF_HEADER.40 (20)
RF_PWR: R9.1, R11.1, RF_HEADER.27 (7), RF_HEADER.29 (9)
RST: C8.2, JP1.4, R12.1, U1.4
SCK: JP2.5, RF_HEADER.16, U1.10
VCORE: C2.1, JP2.2, R10.2, U1.13
VIN_3.6V: C1.1, C3.1, JP1.8, R1.1, R2.1, R9.2, RF_HEADER.39 (19), U1.1

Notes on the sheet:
1.0
RF430CL330H Evaluation Board
Antenna Coil
External Antenna
RF1
RF2
DNP for SPI
Wake Circuit

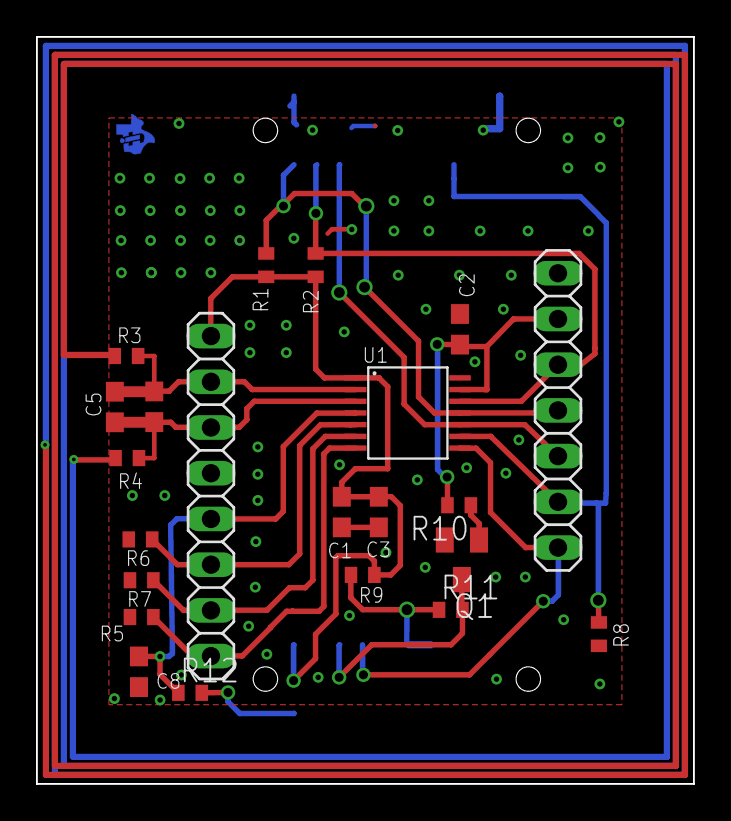
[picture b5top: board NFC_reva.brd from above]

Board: 4 copper layers, 36.5 x 41.5 mm, 24 parts (1 on the bottom side), 18 nets.

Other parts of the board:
U$4: MSP430_LAB_TILOGO_SMALL

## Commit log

2017-11-13 Initial commit of hardware.
2017-11-13 Removed old and in progress harvesters.

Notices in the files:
parts and their libraries:
SparkFun-Connectors: Licensing: Creative Commons ShareAlike 4.0 International - https://creativecommons.org/licenses/by-sa/4.0
SparkFun-DiscreteSemi: Licensing: CC v3.0 Share-Alike You are welcome to use this library for commercial purposes.
